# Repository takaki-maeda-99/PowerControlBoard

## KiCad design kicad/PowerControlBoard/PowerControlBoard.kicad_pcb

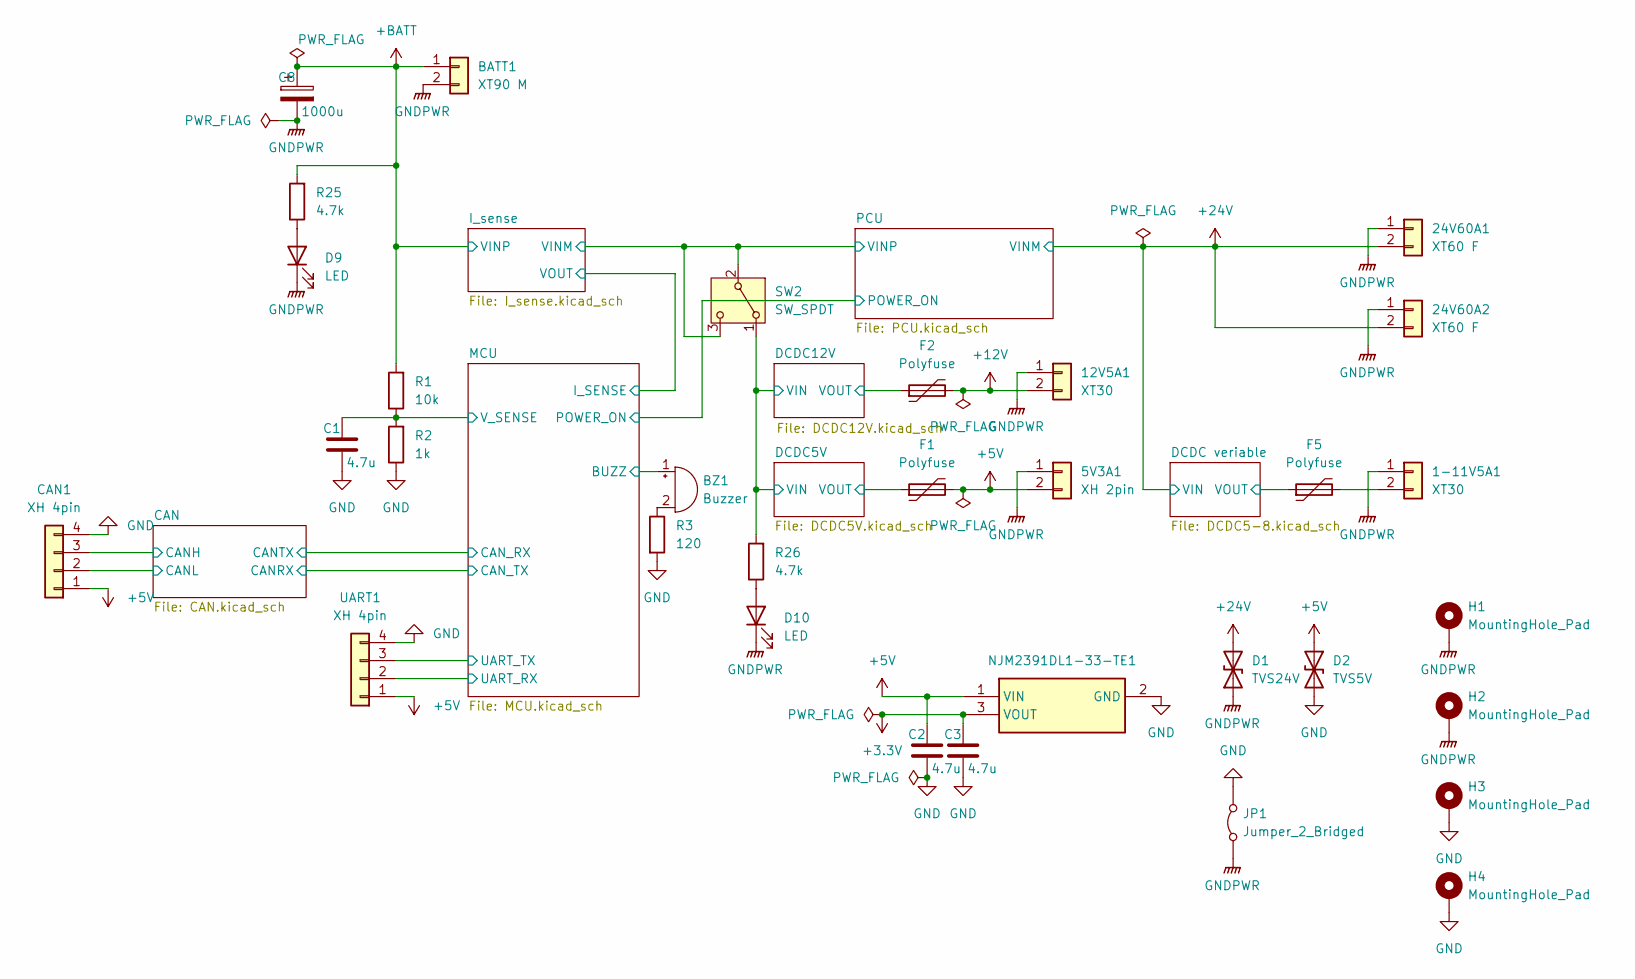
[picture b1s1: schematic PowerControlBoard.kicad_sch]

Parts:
1-11V5A1, 12V5A1: XT30; XT30UPBF
5V3A1: XH 2pin; JST_XH_S2B-XH-A_1x02_P2.50mm_Horizontal
24V60A1, 24V60A2: XT60 F; AMASS_XT60-F_1x02_P7.20mm_Vertical
BATT1: XT90 M; XT90PBF
BZ1: Buzzer; Buzzer_CUI_CPT-9019S-SMT
C1, C2, C3: 4.7u; C_0603_1608Metric
C8: 1000u; CP_Radial_D12.5mm_P5.00mm
CAN1: XH 4pin; JST_XH_S4B-XH-A_1x04_P2.50mm_Horizontal
D1: TVS24V; TO-277A
D2: TVS5V; D_SMB
D9, D10: LED; LED_0603_1608Metric
F1, F2, F5: Polyfuse; Fuse_Bourns_MF-RG500
H1, H2, H3, H4: MountingHole_Pad; MountingHole_3.2mm_M3_Pad
IC1: NJM2391DL1-33-TE1; NJM2391DL133TE1; Mouser Part Number 513-NJM2391DL133-TE1
JP1: Jumper_2_Bridged; SolderJumper-2_P1.3mm_Bridged2Bar_RoundedPad1.0x1.5mm
R1: 10k; R_0603_1608Metric
R2: 1k; R_0603_1608Metric
R3: 120; R_0603_1608Metric
R25, R26: 4.7k; C_0603_1608Metric
SW2: SW_SPDT; FanPinHeader_1x03_P2.54mm_Vertical
UART1: XH 4pin; JST_XH_S4B-XH-A_1x04_P2.50mm_Horizontal

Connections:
+3.3V: C3.1, IC1.3 (VOUT); also elsewhere on the board
+5V: 5V3A1.2, C2.1, CAN1.1, D2.1 (A1), F1.2, IC1.1 (VIN), UART1.1; also elsewhere on the board
+12V: 12V5A1.2, F2.2
+24V: 24V60A1.2, 24V60A2.2, D1.2 (A2); also elsewhere on the board
+BATT: BATT1.1, C8.1, R1.2, R25.2; also elsewhere on the board
/CAN/CANH: CAN1.3; also elsewhere on the board
/CAN/CANL: CAN1.2; also elsewhere on the board
/DCDC5V/VOUT: F1.1; also elsewhere on the board
/DCDC12V/VIN: R26.2, SW2.1 (A); also elsewhere on the board
/DCDC12V/VOUT: F2.1; also elsewhere on the board
/DCDC veriable/VOUT: F5.1; also elsewhere on the board
/I_sense/VINM: SW2.2 (B), SW2.3 (C); also elsewhere on the board
/MCU/BUZZ: BZ1.1 (+); also elsewhere on the board
/MCU/UART_RX: UART1.2; also elsewhere on the board
/MCU/UART_TX: UART1.3; also elsewhere on the board
/MCU/V_SENSE: C1.1, R1.1, R2.2; also elsewhere on the board
GND: C1.2, C2.2, C3.2, CAN1.4, D2.2 (A2), H3.1, H4.1, IC1.2 (GND), JP1.2 (B), R2.1, R3.2, UART1.4; also elsewhere on the board
GNDPWR: 1-11V5A1.1, 5V3A1.1, 12V5A1.1, 24V60A1.1, 24V60A2.1, BATT1.2, C8.2, D1.1 (A1), D9.1 (K), D10.1 (K), H1.1, H2.1, JP1.1 (A); also elsewhere on the board
unnamed: 1-11V5A1.2, F5.2
unnamed: BZ1.2 (-), R3.1
unnamed: D9.2 (A), R25.1
unnamed: D10.2 (A), R26.1

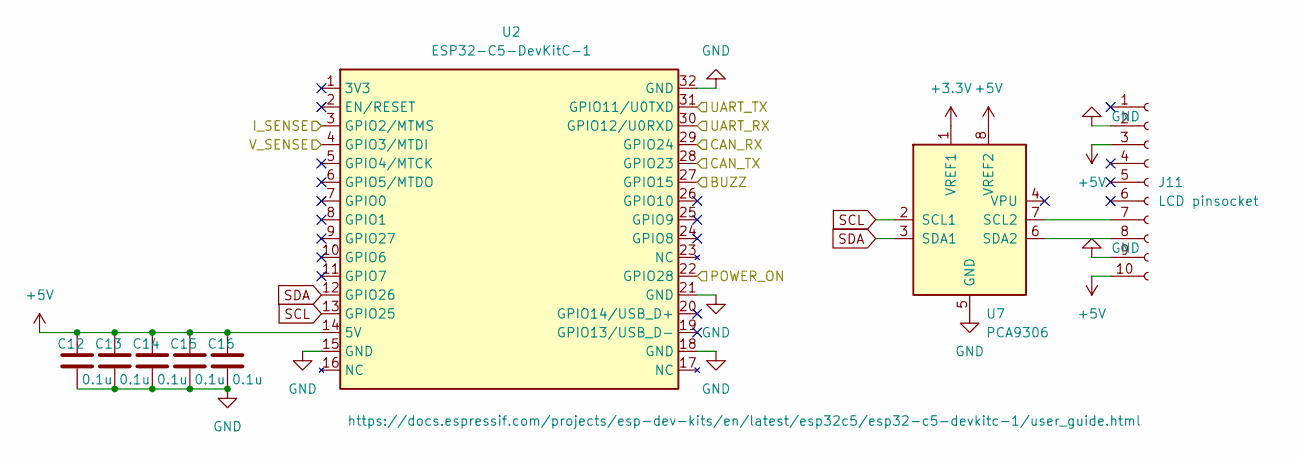
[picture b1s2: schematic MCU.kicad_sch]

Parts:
C12, C13, C14, C15, C16: 0.1u; C_0603_1608Metric
J11: LCD pinsocket; PinSocket_1x10_P2.54mm_Vertical
U2: ESP32-C5-DevKitC-1
U7: PCA9306; DIP-8_W10.16mm

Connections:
+3.3V: U7.1 (VREF1); also elsewhere on the board
+5V: C12.1, C13.1, C14.1, C15.1, C16.1, J11.3, J11.10, U2.14 (5V), U7.8 (VREF2); also elsewhere on the board
/CAN/CANRX: U2.28 (GPIO23); also elsewhere on the board
/CAN/CANTX: U2.29 (GPIO24); also elsewhere on the board
/I_sense/VOUT: U2.3 (GPIO2/MTMS); also elsewhere on the board
/MCU/BUZZ: U2.27 (GPIO15); also elsewhere on the board
/MCU/POWER_ON: U2.22 (GPIO28); also elsewhere on the board
/MCU/UART_RX: U2.30 (GPIO12/U0RXD); also elsewhere on the board
/MCU/UART_TX: U2.31 (GPIO11/U0TXD); also elsewhere on the board
/MCU/V_SENSE: U2.4 (GPIO3/MTDI); also elsewhere on the board
GND: C12.2, C13.2, C14.2, C15.2, C16.2, J11.2, J11.9, U2.15 (GND), U2.18 (GND), U2.21 (GND), U2.32 (GND), U7.5 (GND); also elsewhere on the board
unnamed: J11.7, U7.7 (SCL2)
unnamed: J11.8, U7.6 (SDA2)
SCL: U2.13 (GPIO25), U7.2 (SCL1)
SDA: U2.12 (GPIO26), U7.3 (SDA1)

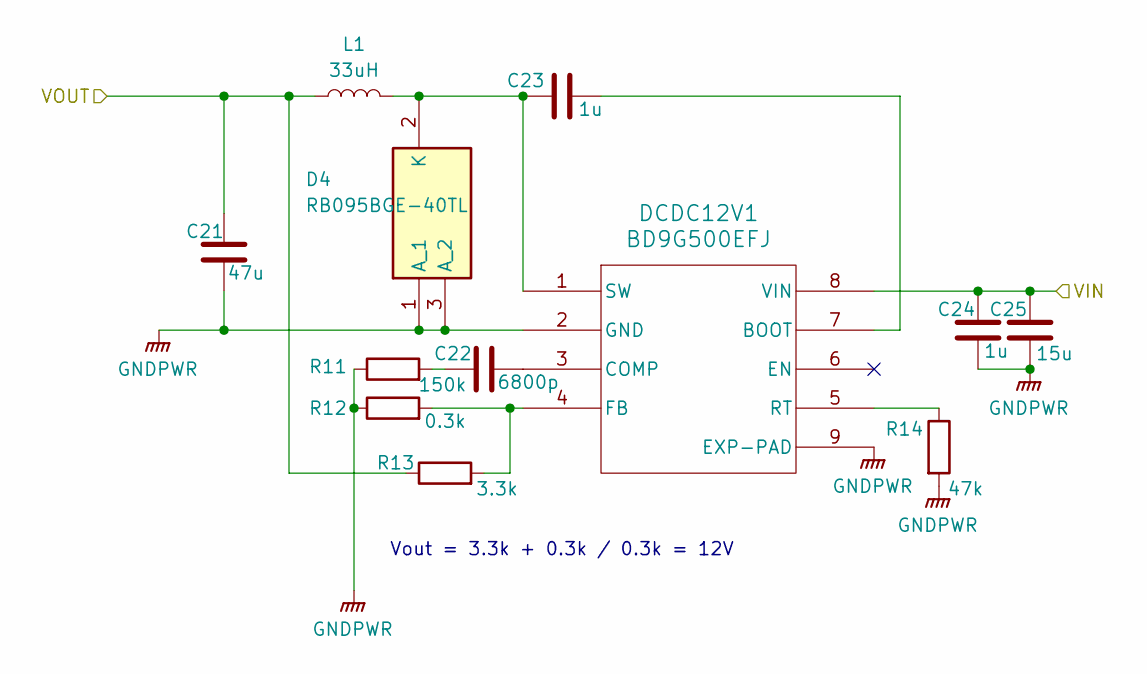
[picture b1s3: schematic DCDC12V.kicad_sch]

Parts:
C21: 47u; C_1206_3216Metric
C22: 6800p; C_0603_1608Metric
C23, C24: 1u; C_0603_1608Metric
C25: 15u; C_2220_5750Metric
D4: RB095BGE-40TL; RD3P175SNFRATL; Manufacturer_Part_Number RB095BGE-40TL; Mouser Part Number 755-RB095BGE-40TL
DCDC12V1: BD9G500EFJ; HTSOP-J8
L1: 33uH; IND_CSEB0660H-330M
R11: 150k; R_0603_1608Metric
R12: 0.3k; R_0603_1608Metric
R13: 3.3k; R_0603_1608Metric
R14: 47k; R_0603_1608Metric

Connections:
/DCDC12V/VIN: C24.1, C25.1, DCDC12V1.8 (VIN); also elsewhere on the board
/DCDC12V/VOUT: C21.2, L1.1, R13.1; also elsewhere on the board
GNDPWR: C21.1, C24.2, C25.2, D4.1 (A_1), D4.3 (A_2), DCDC12V1.2 (GND), DCDC12V1.9 (EXP-PAD), R11.1, R12.1, R14.2; also elsewhere on the board
unnamed: C22.1, R11.2
unnamed: C23.1, D4.2 (K), DCDC12V1.1 (SW), L1.2
unnamed: C23.2, DCDC12V1.7 (BOOT)
unnamed: C22.2, DCDC12V1.3 (COMP)
unnamed: DCDC12V1.4 (FB), R12.2, R13.2
unnamed: DCDC12V1.5 (RT), R14.1

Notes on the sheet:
Vout = 3.3k + 0.3k / 0.3k = 12V

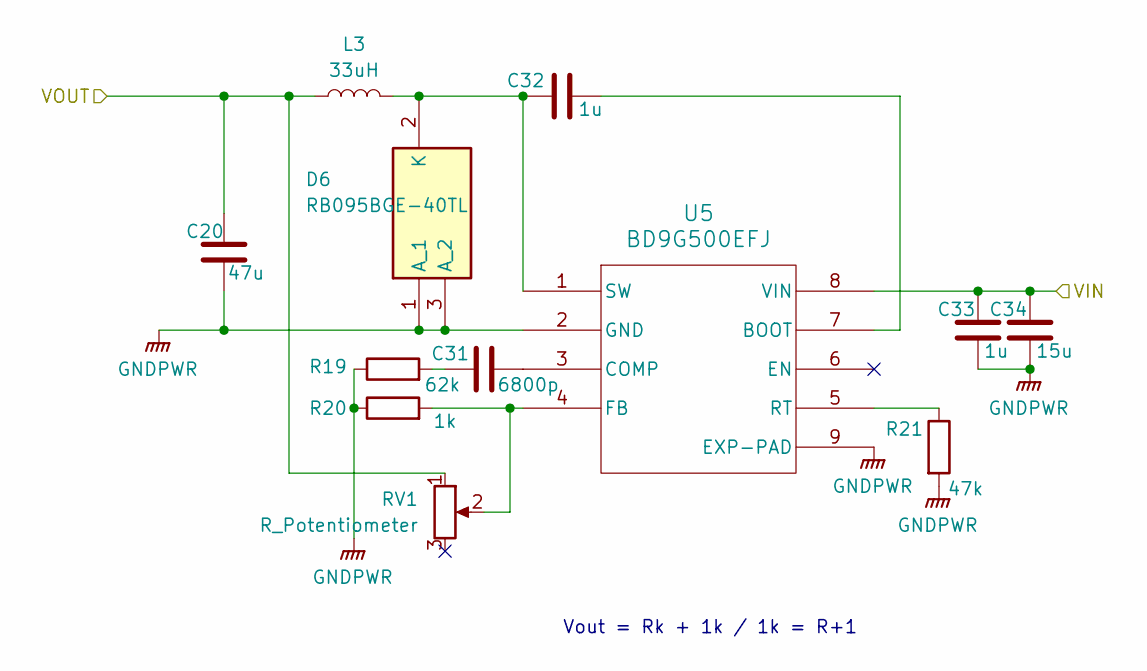
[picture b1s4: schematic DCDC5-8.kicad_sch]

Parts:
C20: 47u; C_1206_3216Metric
C31: 6800p; C_0603_1608Metric
C32, C33: 1u; C_0603_1608Metric
C34: 15u; C_2220_5750Metric
D6: RB095BGE-40TL; RD3P175SNFRATL; Manufacturer_Part_Number RB095BGE-40TL; Mouser Part Number 755-RB095BGE-40TL
L3: 33uH; IND_CSEB0660H-330M
R19: 62k; R_0603_1608Metric
R20: 1k; R_0603_1608Metric
R21: 47k; R_0603_1608Metric
RV1: R_Potentiometer; Potentiometer_Bourns_3386P_Vertical
U5: BD9G500EFJ; HTSOP-J8

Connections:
+24V: C33.1, C34.1, U5.8 (VIN); also elsewhere on the board
/DCDC veriable/VOUT: C20.2, L3.1, RV1.1; also elsewhere on the board
GNDPWR: C20.1, C33.2, C34.2, D6.1 (A_1), D6.3 (A_2), R19.1, R20.1, R21.2, U5.2 (GND), U5.9 (EXP-PAD); also elsewhere on the board
unnamed: C31.1, R19.2
unnamed: C32.1, D6.2 (K), L3.2, U5.1 (SW)
unnamed: C32.2, U5.7 (BOOT)
unnamed: C31.2, U5.3 (COMP)
unnamed: R20.2, RV1.2, U5.4 (FB)
unnamed: R21.1, U5.5 (RT)

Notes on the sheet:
Vout = Rk + 1k / 1k = R+1

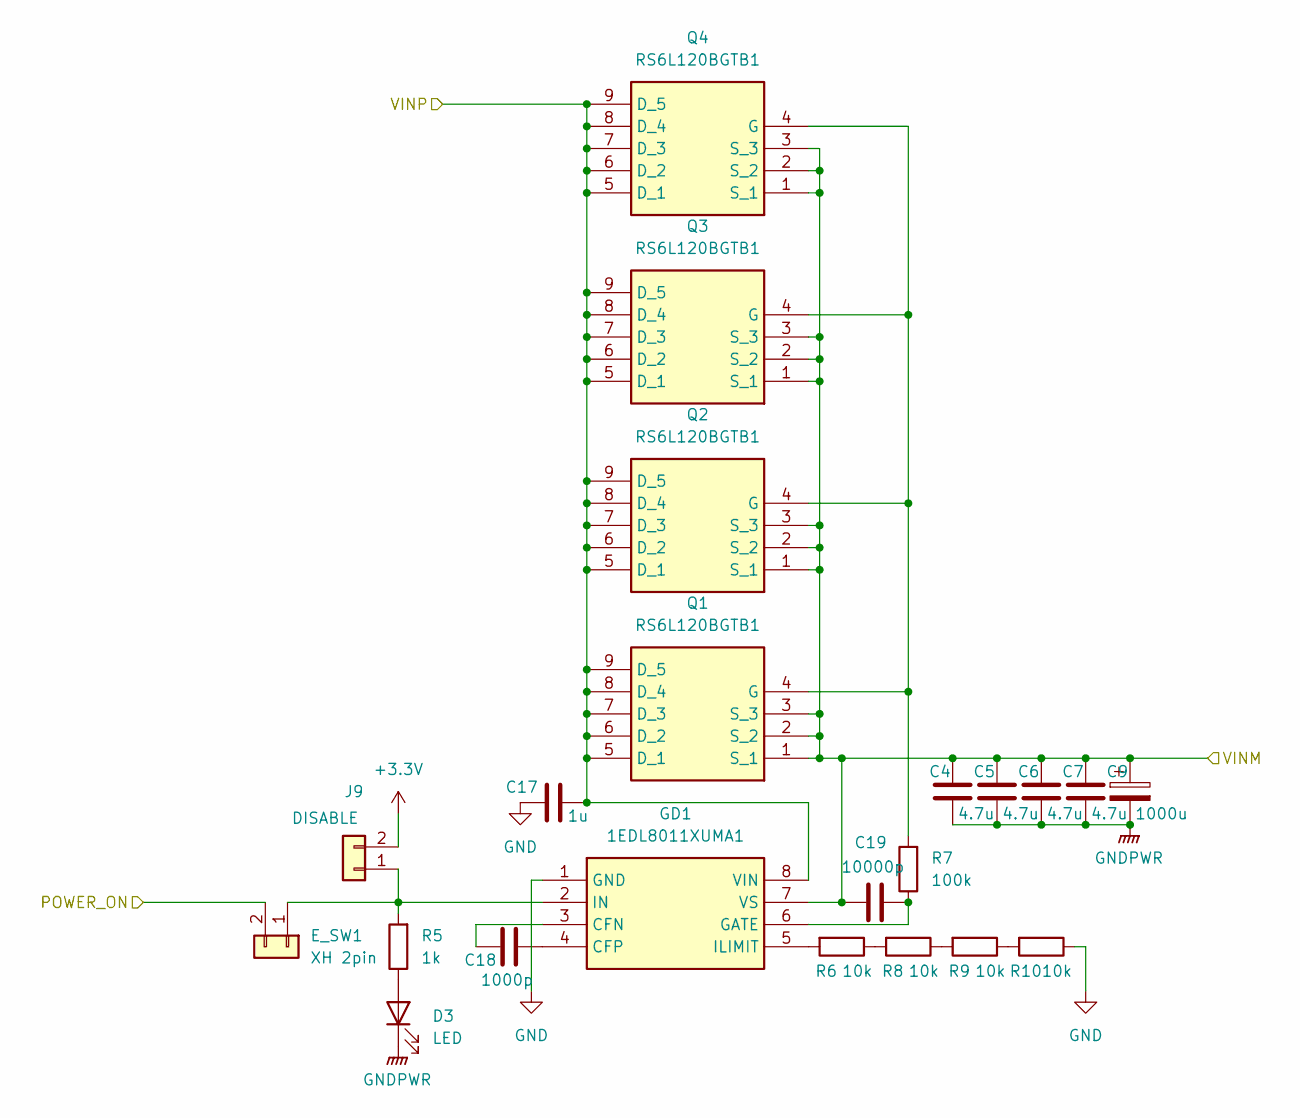
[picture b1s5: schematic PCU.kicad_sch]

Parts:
C4, C5, C6, C7: 4.7u; C_0603_1608Metric
C9: 1000u; CP_Radial_D12.5mm_P5.00mm
C17: 1u; C_0603_1608Metric
C18: 1000p; C_0603_1608Metric
C19: 10000p; C_0603_1608Metric
D3: LED; LED_0603_1608Metric
E_SW1: XH 2pin; JST_XH_B2B-XH-A_1x02_P2.50mm_Vertical
GD1: 1EDL8011XUMA1; SOIC127P600X175-8N; Mouser Part Number 726-1EDL8011XUMA1
J9: DISABLE; PinHeader_1x02_P2.54mm_Vertical
Q1, Q2, Q3, Q4: RS6L120BGTB1; RS1L151ATTB1; Manufacturer_Part_Number RS6L120BGTB1; Mouser Part Number 755-RS6L120BGTB1
R5: 1k; R_0603_1608Metric
R6, R8, R9, R10: 10k; R_0603_1608Metric
R7: 100k; R_0603_1608Metric

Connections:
+3.3V: J9.2; also elsewhere on the board
+24V: C4.1, C5.1, C6.1, C7.1, C9.1, C19.1, GD1.7 (VS), Q1.1 (S_1), Q1.2 (S_2), Q1.3 (S_3), Q2.1 (S_1), Q2.2 (S_2), Q2.3 (S_3), Q3.1 (S_1), Q3.2 (S_2), Q3.3 (S_3), Q4.1 (S_1), Q4.2 (S_2), Q4.3 (S_3); also elsewhere on the board
/I_sense/VINM: C17.1, GD1.8 (VIN), Q1.5 (D_1), Q1.6 (D_2), Q1.7 (D_3), Q1.8 (D_4), Q1.9 (D_5), Q2.5 (D_1), Q2.6 (D_2), Q2.7 (D_3), Q2.8 (D_4), Q2.9 (D_5), Q3.5 (D_1), Q3.6 (D_2), Q3.7 (D_3), Q3.8 (D_4), Q3.9 (D_5), Q4.5 (D_1), Q4.6 (D_2), Q4.7 (D_3), Q4.8 (D_4), Q4.9 (D_5); also elsewhere on the board
/MCU/POWER_ON: E_SW1.2; also elsewhere on the board
GND: C17.2, GD1.1 (GND), R10.1; also elsewhere on the board
GNDPWR: C4.2, C5.2, C6.2, C7.2, C9.2, D3.1 (K); also elsewhere on the board
unnamed: D3.2 (A), R5.1
unnamed: E_SW1.1, GD1.2 (IN), J9.1, R5.2
unnamed: C18.1, GD1.3 (CFN)
unnamed: C18.2, GD1.4 (CFP)
unnamed: C19.2, GD1.6 (GATE), R7.1
unnamed: GD1.5 (ILIMIT), R6.2
unnamed: Q1.4 (G), Q2.4 (G), Q3.4 (G), Q4.4 (G), R7.2
unnamed: R6.1, R8.2
unnamed: R8.1, R9.2
unnamed: R9.1, R10.2

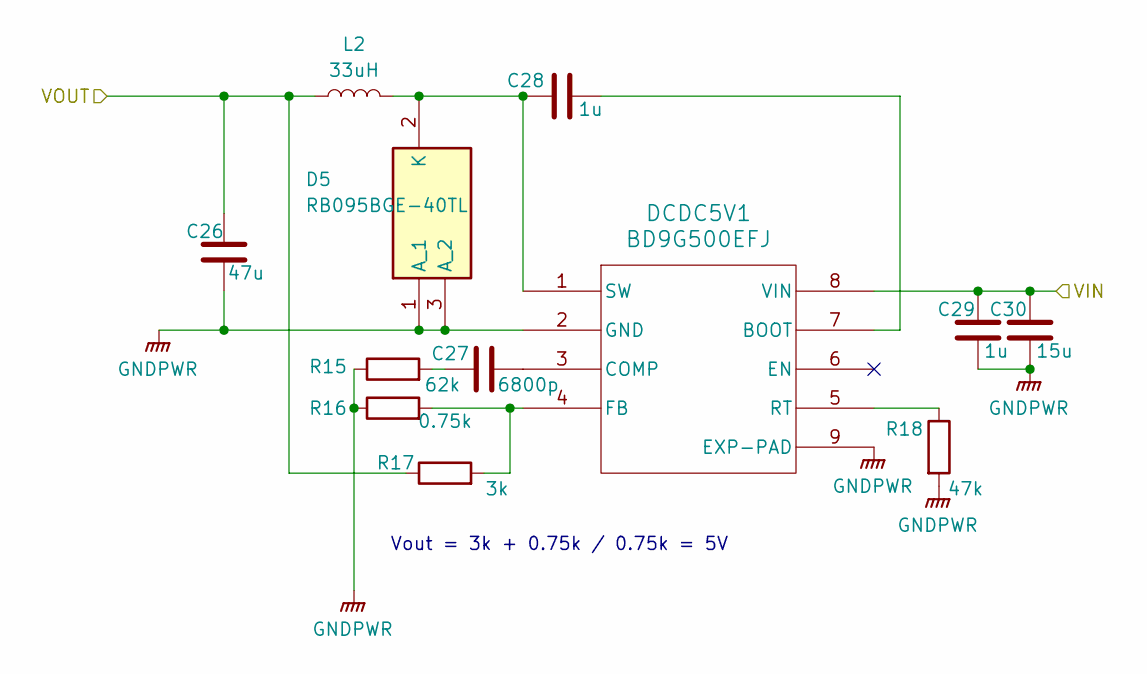
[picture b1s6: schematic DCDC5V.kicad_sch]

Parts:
C26: 47u; C_1206_3216Metric
C27: 6800p; C_0603_1608Metric
C28, C29: 1u; C_0603_1608Metric
C30: 15u; C_2220_5750Metric
D5: RB095BGE-40TL; RD3P175SNFRATL; Manufacturer_Part_Number RB095BGE-40TL; Mouser Part Number 755-RB095BGE-40TL
DCDC5V1: BD9G500EFJ; HTSOP-J8
L2: 33uH; IND_CSEB0660H-330M
R15: 62k; R_0603_1608Metric
R16: 0.75k; R_0603_1608Metric
R17: 3k; R_0603_1608Metric
R18: 47k; R_0603_1608Metric

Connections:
/DCDC5V/VOUT: C26.2, L2.1, R17.1; also elsewhere on the board
/DCDC12V/VIN: C29.1, C30.1, DCDC5V1.8 (VIN); also elsewhere on the board
GNDPWR: C26.1, C29.2, C30.2, D5.1 (A_1), D5.3 (A_2), DCDC5V1.2 (GND), DCDC5V1.9 (EXP-PAD), R15.1, R16.1, R18.2; also elsewhere on the board
unnamed: C27.1, R15.2
unnamed: C28.1, D5.2 (K), DCDC5V1.1 (SW), L2.2
unnamed: C28.2, DCDC5V1.7 (BOOT)
unnamed: C27.2, DCDC5V1.3 (COMP)
unnamed: DCDC5V1.4 (FB), R16.2, R17.2
unnamed: DCDC5V1.5 (RT), R18.1

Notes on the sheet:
Vout = 3k + 0.75k / 0.75k = 5V

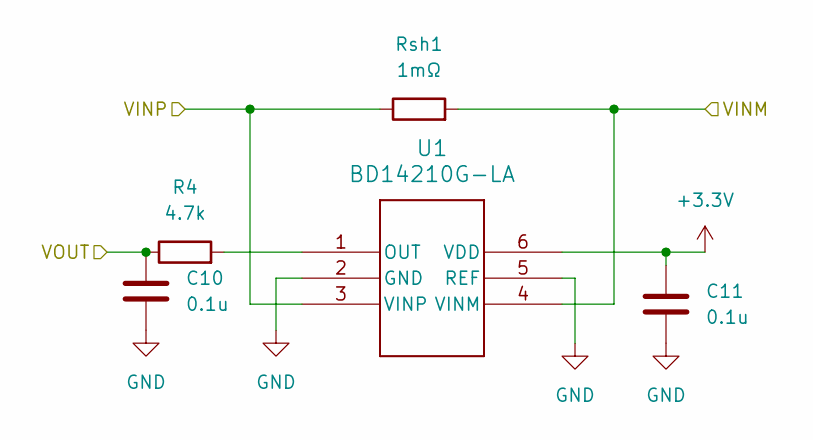
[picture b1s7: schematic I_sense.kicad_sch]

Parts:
C10, C11: 0.1u; C_0603_1608Metric
R4: 4.7k; R_0603_1608Metric
Rsh1: 1mΩ; R_2512_6332Metric
U1: BD14210G-LA; SSOP6

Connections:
+3.3V: C11.1, U1.6 (VDD); also elsewhere on the board
+BATT: Rsh1.1, U1.3 (VINP); also elsewhere on the board
/I_sense/VINM: Rsh1.2, U1.4 (VINM); also elsewhere on the board
/I_sense/VOUT: C10.1, R4.1; also elsewhere on the board
GND: C10.2, C11.2, U1.2 (GND), U1.5 (REF); also elsewhere on the board
unnamed: R4.2, U1.1 (OUT)

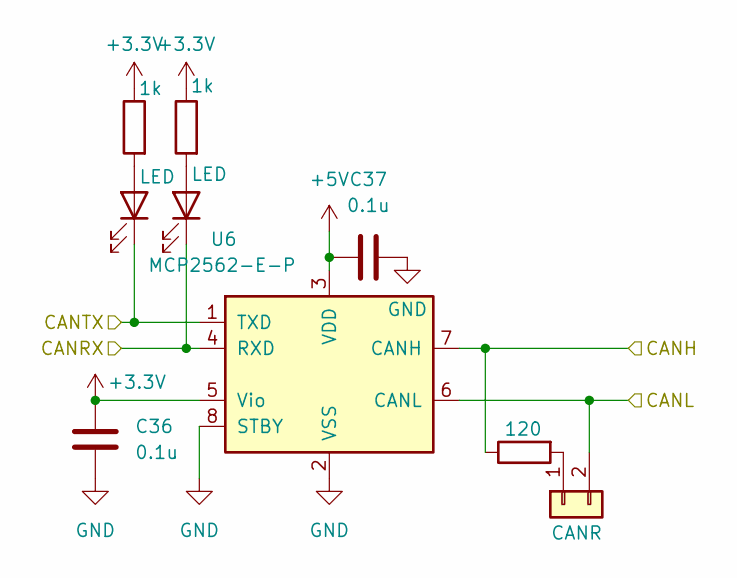
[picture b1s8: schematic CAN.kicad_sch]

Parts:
C36, C37: 0.1u; C_0603_1608Metric
D7, D8: LED; LED_0603_1608Metric
J10: CANR; PinHeader_1x02_P2.54mm_Vertical
R22, R23: 1k; R_0603_1608Metric
R24: 120; R_0603_1608Metric
U6: MCP2562-E-P; DIP-8_W7.62mm

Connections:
+3.3V: C36.2, R22.1, R23.1, U6.5 (Vio); also elsewhere on the board
+5V: C37.2, U6.3 (VDD); also elsewhere on the board
/CAN/CANH: R24.1, U6.7 (CANH); also elsewhere on the board
/CAN/CANL: J10.2, U6.6 (CANL); also elsewhere on the board
/CAN/CANRX: D8.1 (K), U6.4 (RXD); also elsewhere on the board
/CAN/CANTX: D7.1 (K), U6.1 (TXD); also elsewhere on the board
GND: C36.1, C37.1, U6.2 (VSS), U6.8 (STBY); also elsewhere on the board
unnamed: D7.2 (A), R22.2
unnamed: D8.2 (A), R23.2
unnamed: J10.1, R24.2

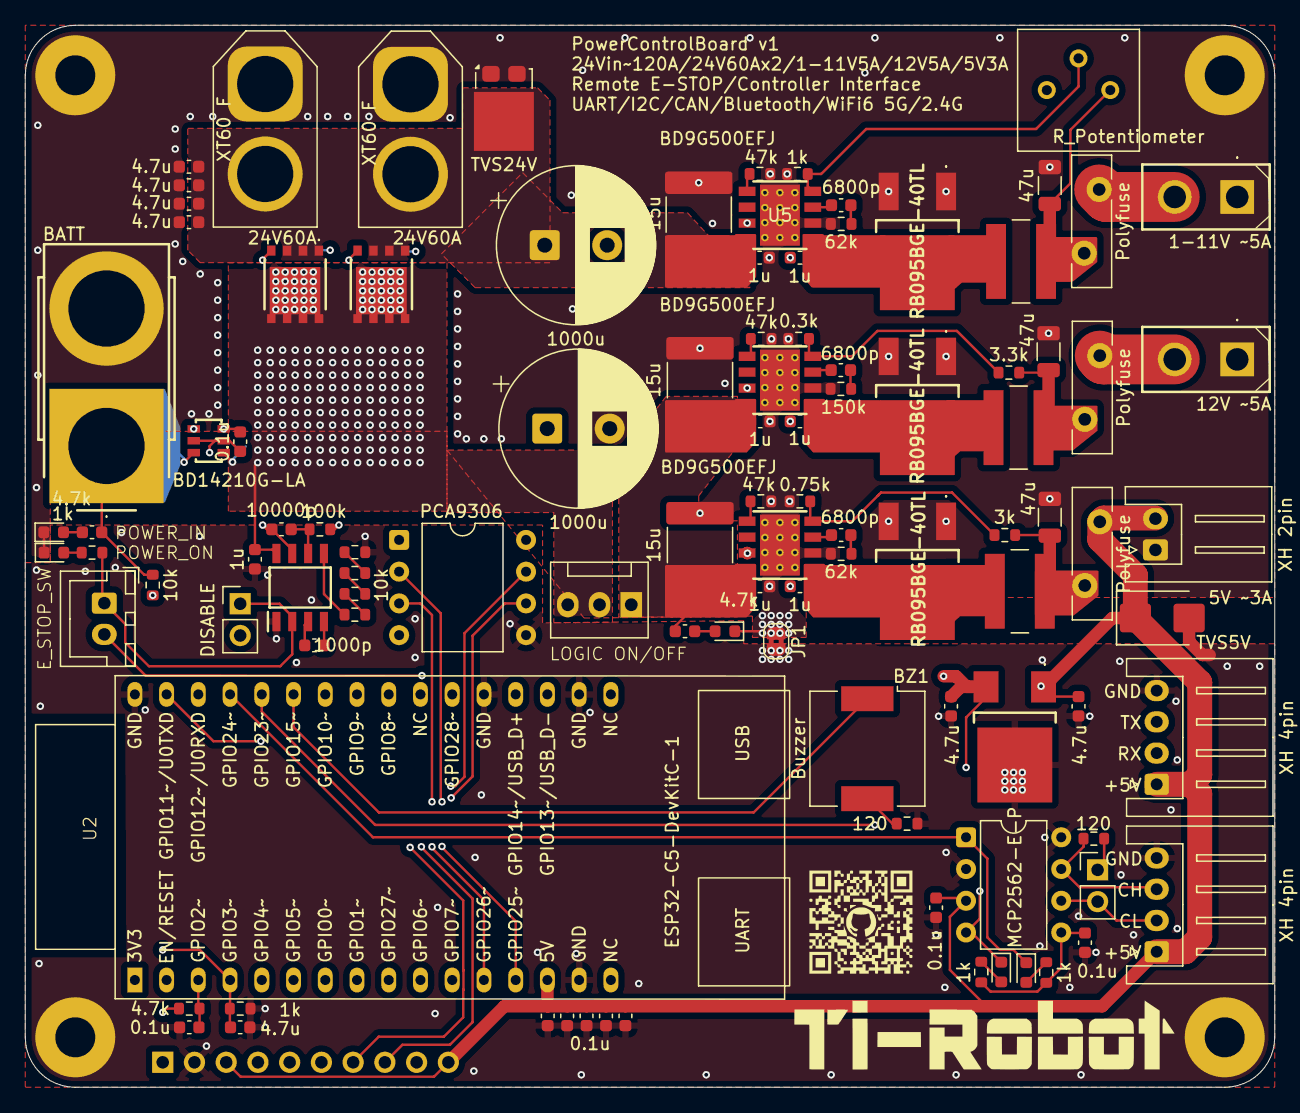
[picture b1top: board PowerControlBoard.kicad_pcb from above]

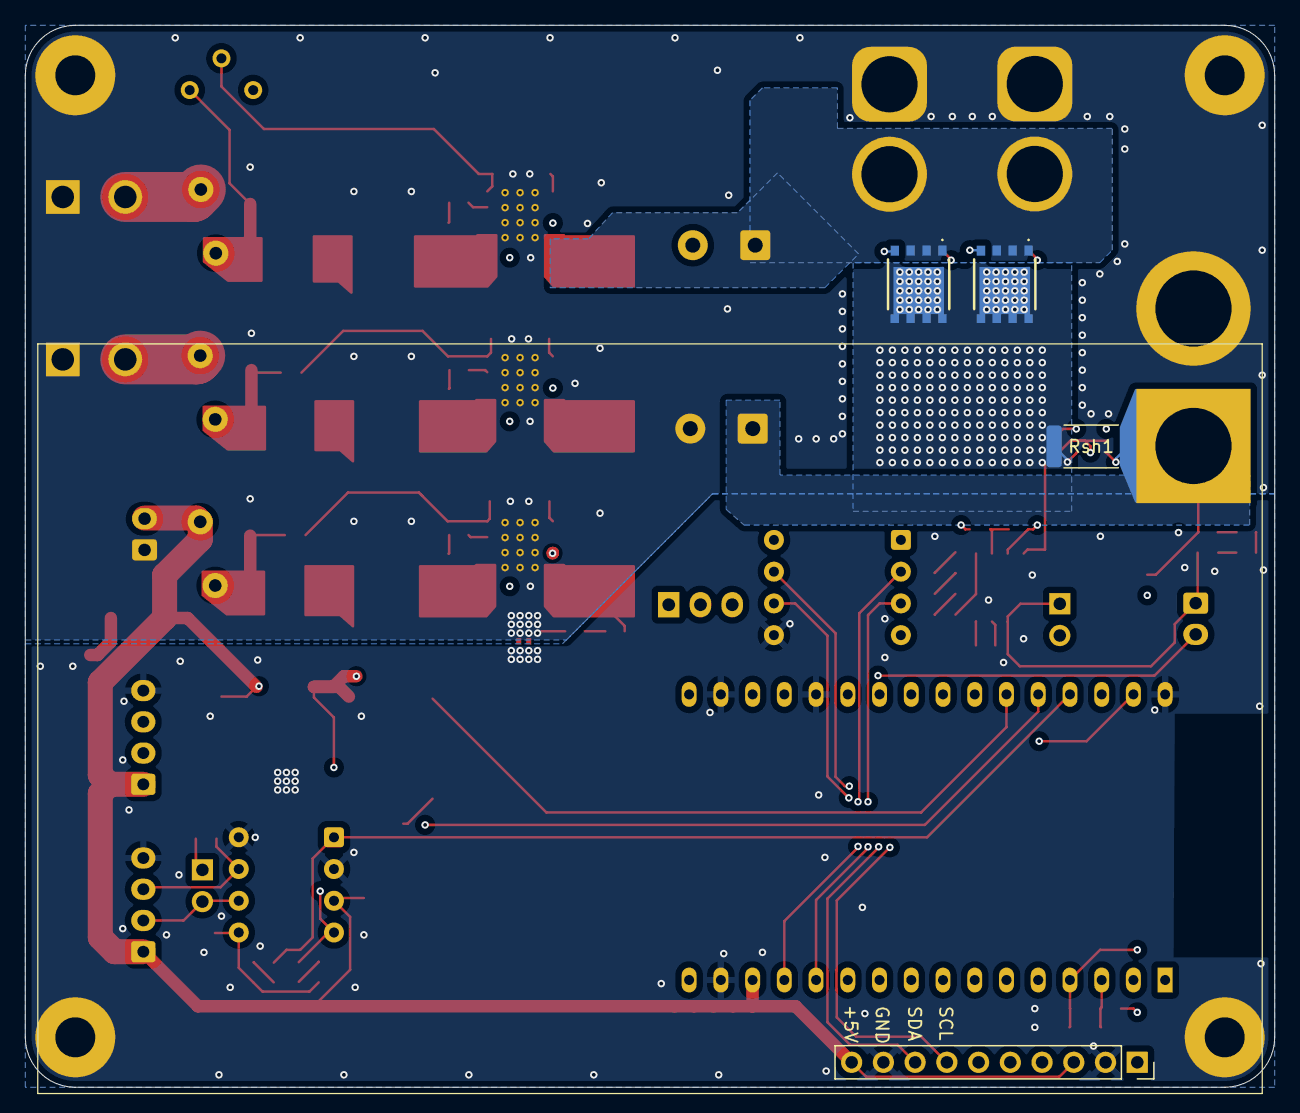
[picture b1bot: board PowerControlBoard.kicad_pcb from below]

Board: 4 copper layers, 100.0 x 85.0 mm, 112 parts (4 on the bottom side), 62 nets.

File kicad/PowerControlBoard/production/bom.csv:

Designator,Footprint,Quantity,Value,LCSC Part #
"1-11V5A1, 12V5A1",XT30UPBF,2,XT30,
"24V60A1, 24V60A2",AMASS_XT60-F_1x02_P7.20mm_Vertical,2,XT60 F,
5V3A1,JST_XH_S2B-XH-A_1x02_P2.50mm_Horizontal,1,XH 2pin,
BATT1,XT90PBF,1,XT90 M,
BZ1,Buzzer_CUI_CPT-9019S-SMT,1,Buzzer,
"C1, C2, C3, C4, C5, C6, C7",0603,7,4.7u,
"C10, C11, C12, C13, C14, C15, C16, C36, C37",0603,9,0.1u,
"C17, C23, C24, C28, C29, C32, C33",0603,7,1u,
C18,0603,1,1000p,
C19,0603,1,10000p,
"C20, C21, C26",1206,3,47u,
"C22, C27, C31",0603,3,6800p,
"C25, C30, C34",2220,3,15u,
"C8, C9",CP_Radial_D12.5mm_P5.00mm,2,1000u,
"CAN1, UART1",JST_XH_S4B-XH-A_1x04_P2.50mm_Horizontal,2,XH 4pin,
D1,TO-277A,1,TVS24V,
"D10, D3, D7, D8, D9",0603,5,LED,
D2,D_SMB,1,TVS5V,
"D4, D5, D6",RD3P175SNFRATL,3,RB095BGE-40TL,
"DCDC12V1, DCDC5V1, U5",HTSOP-J8,3,BD9G500EFJ,
E_SW1,JST_XH_B2B-XH-A_1x02_P2.50mm_Vertical,1,XH 2pin,
"F1, F2, F5",Fuse_Bourns_MF-RG500,3,Polyfuse,
GD1,SOIC127P600X175-8N,1,1EDL8011XUMA1,
IC1,NJM2391DL133TE1,1,NJM2391DL1-33-TE1,
J10,PinHeader_1x02_P2.54mm_Vertical,1,CANR,
J11,PinSocket_1x10_P2.54mm_Vertical,1,LCD pinsocket,
J9,PinHeader_1x02_P2.54mm_Vertical,1,DISABLE,
JP1,SolderJumper-2_P1.3mm_Bridged2Bar_RoundedPad1.0x1.5mm,1,Jumper_2_Bridged,
"L1, L2, L3",IND_CSEB0660H-330M,3,33uH,
"Q1, Q2, Q3, Q4",RS1L151ATTB1,4,RS6L120BGTB1,
"R1, R10, R6, R8, R9",0603,5,10k,
R11,0603,1,150k,
R12,0603,1,0.3k,
R13,0603,1,3.3k,
"R14, R18, R21",0603,3,47k,
"R15, R19",0603,2,62k,
R16,0603,1,0.75k,
R17,0603,1,3k,
"R2, R20, R22, R23, R5",0603,5,1k,
"R24, R3",0603,2,120,
"R25, R26, R4",0603,3,4.7k,
R7,0603,1,100k,
RSH1,2512,1,1mΩ,
RV1,Potentiometer_Bourns_3386P_Vertical,1,R_Potentiometer,
SW2,FanPinHeader_1x03_P2.54mm_Vertical,1,SW_SPDT,
U1,SSOP6,1,BD14210G-LA,
U2,ESP32-C5-DevKitC-1,1,ESP32-C5-DevKitC-1,
U6,DIP-8_W7.62mm,1,MCP2562-E-P,
U7,DIP-8_W10.16mm,1,PCA9306,

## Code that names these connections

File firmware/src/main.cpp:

#include <Arduino.h>
#include <ps5Controller.h>

enum SystemState {
  READY = 0,
  OVERCURRENT = 1,
  UNDERVOLTAGE = 2,
  NOT_CONNECTED = 3,
  E_STOP = 4
};

const int8_t CAN_RX = 19;
const int8_t CAN_TX = 18;
const int8_t UART_RX = 22;
const int8_t UART_TX = 23;
const int8_t BUZZ = 17;
const int8_t POWER_ON = 16;
const int8_t V_SENSE = 35;
const int8_t I_SENSE = 34;

void buzzPattern(int count, int on_time, int off_time) {
  for(int i = 0; i < count; i++) {
    analogWrite(BUZZ, 250);
    delay(on_time);
    analogWrite(BUZZ, 0);
    delay(off_time);
  }
}

void setup() {
  Serial.begin(115200);
  Serial2.begin(115200, SERIAL_8N1, UART_RX, UART_TX);
  pinMode(V_SENSE, INPUT);
  pinMode(I_SENSE, INPUT);
  pinMode(POWER_ON, OUTPUT);
  digitalWrite(POWER_ON, HIGH);
  ps5.begin("4c:b9:9b:8a:c3:07");

  buzzPattern(3, 100, 100);
}


void loop() {
  float i_sense = analogRead(I_SENSE);//*3.3/(4095.0*0.001*20.0);
  float v_sense = analogRead(V_SENSE)*3.3*11.2/4095.0;
  SystemState state = NOT_CONNECTED;
  
  if(digitalRead(POWER_ON) == HIGH) {
    if(i_sense > 100){
      state = OVERCURRENT;
      digitalWrite(POWER_ON, LOW);
      buzzPattern(1, 100, 100);
    } 
    else if(v_sense < 22.0){
      state = UNDERVOLTAGE;
      digitalWrite(POWER_ON, LOW);
      buzzPattern(1, 500, 500);
    }
  }
  
  if(!ps5.isConnected()) {
    state = NOT_CONNECTED;
    digitalWrite(POWER_ON, LOW);
    buzzPattern(2, 100, 500);
  }
  else if(digitalRead(POWER_ON) == LOW) {
    state = E_STOP;
  }
  else {
    state = READY;
  }
  
  uint16_t buttons = 0;
  int16_t lx = 0, ly = 0, rx = 0, ry = 0;
  uint8_t l2 = 0, r2 = 0;
  
  if (ps5.isConnected()) {
    buttons |= ps5.Square() << 0;
    buttons |= ps5.Cross() << 1;
    buttons |= ps5.Circle() << 2;
    buttons |= ps5.Triangle() << 3;
    buttons |= ps5.L1() << 4;
    buttons |= ps5.R1() << 5;
    buttons |= ps5.L3() << 6;
    buttons |= ps5.R3() << 7;
    buttons |= ps5.Share() << 8;
    buttons |= ps5.Options() << 9;
    buttons |= ps5.PSButton() << 10;
    buttons |= ps5.Touchpad() << 11;
    buttons |= ps5.Up() << 12;
    buttons |= ps5.Down() << 13;
    buttons |= ps5.Left() << 14;
    buttons |= ps5.Right() << 15;
    
    lx = ps5.LStickX();
    ly = ps5.LStickY();
    rx = ps5.RStickX();
    ry = ps5.RStickY();
    
    const int8_t deadzone = 10;
    if (abs(lx) < deadzone) lx = 0;
    if (abs(ly) < deadzone) ly = 0;
    if (abs(rx) < deadzone) rx = 0;
    if (abs(ry) < deadzone) ry = 0;
    l2 = ps5.L2Value();
    r2 = ps5.R2Value();
    
    if (ps5.Touchpad()) {
      digitalWrite(POWER_ON, !digitalRead(POWER_ON));
      buzzPattern(1, 500, 0);
    }
  }
  
  Serial2.printf("%d,%u,%d,%d,%d,%d,%u,%u\n", 
                 state, buttons, lx, ly, rx, ry, l2, r2);

  Serial.printf("I_Sense: %.2f A, V_Sense: %.2f V", i_sense, v_sense);

  Serial.printf("%d,%u,%d,%d,%d,%d,%u,%u\n", 
                state, buttons, lx, ly, rx, ry, l2, r2);
  
  // 受信側マイコンでの処理例:
  // if(Serial.available()) {
  //   String data = Serial.readStringUntil('\n');
  //   int values[8];
  //   int index = 0;
  //   char* token = strtok(data.c_str(), ",");
  //   while(token && index < 8) {
  //     values[index++] = atoi(token);
  //     token = strtok(NULL, ",");
  //   }
  //   // values[0]: state (0=READY, 1=OVERCURRENT, 2=UNDERVOLTAGE, 3=NOT_CONNECTED, 4=E_STOP)
  //   // values[1]: buttons ビット配置
  //   // values[2]: lx (-128~127), values[3]: ly (-128~127)
  //   // values[4]: rx (-128~127), values[5]: ry (-128~127)
  //   // values[6]: l2 (0~255), values[7]: r2 (0~255)
  //   
  //   if(values[1] & (1<<0)) Serial.println("Square pressed");
  //   if(values[1] & (1<<1)) Serial.println("Cross pressed");
  //   if(values[1] & (1<<2)) Serial.println("Circle pressed");
  //   if(values[1] & (1<<3)) Serial.println("Triangle pressed");
  //   if(values[1] & (1<<4)) Serial.println("L1 pressed");
  //   if(values[1] & (1<<5)) Serial.println("R1 pressed");
  //   if(values[1] & (1<<6)) Serial.println("L3 pressed");
  //   if(values[1] & (1<<7)) Serial.println("R3 pressed");
  //   if(values[1] & (1<<8)) Serial.println("Share pressed");
  //   if(values[1] & (1<<9)) Serial.println("Options pressed");
  //   if(values[1] & (1<<10)) Serial.println("PS pressed");
  //   if(values[1] & (1<<11)) Serial.println("Touchpad pressed");
  //   if(values[1] & (1<<12)) Serial.println("Up pressed");
  //   if(values[1] & (1<<13)) Serial.println("Down pressed");
  //   if(values[1] & (1<<14)) Serial.println("Left pressed");
  //   if(values[1] & (1<<15)) Serial.println("Right pressed");
  // }
  
  delay(50);

}

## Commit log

2025-08-22 add deadzone
2025-08-26 can_protocol
